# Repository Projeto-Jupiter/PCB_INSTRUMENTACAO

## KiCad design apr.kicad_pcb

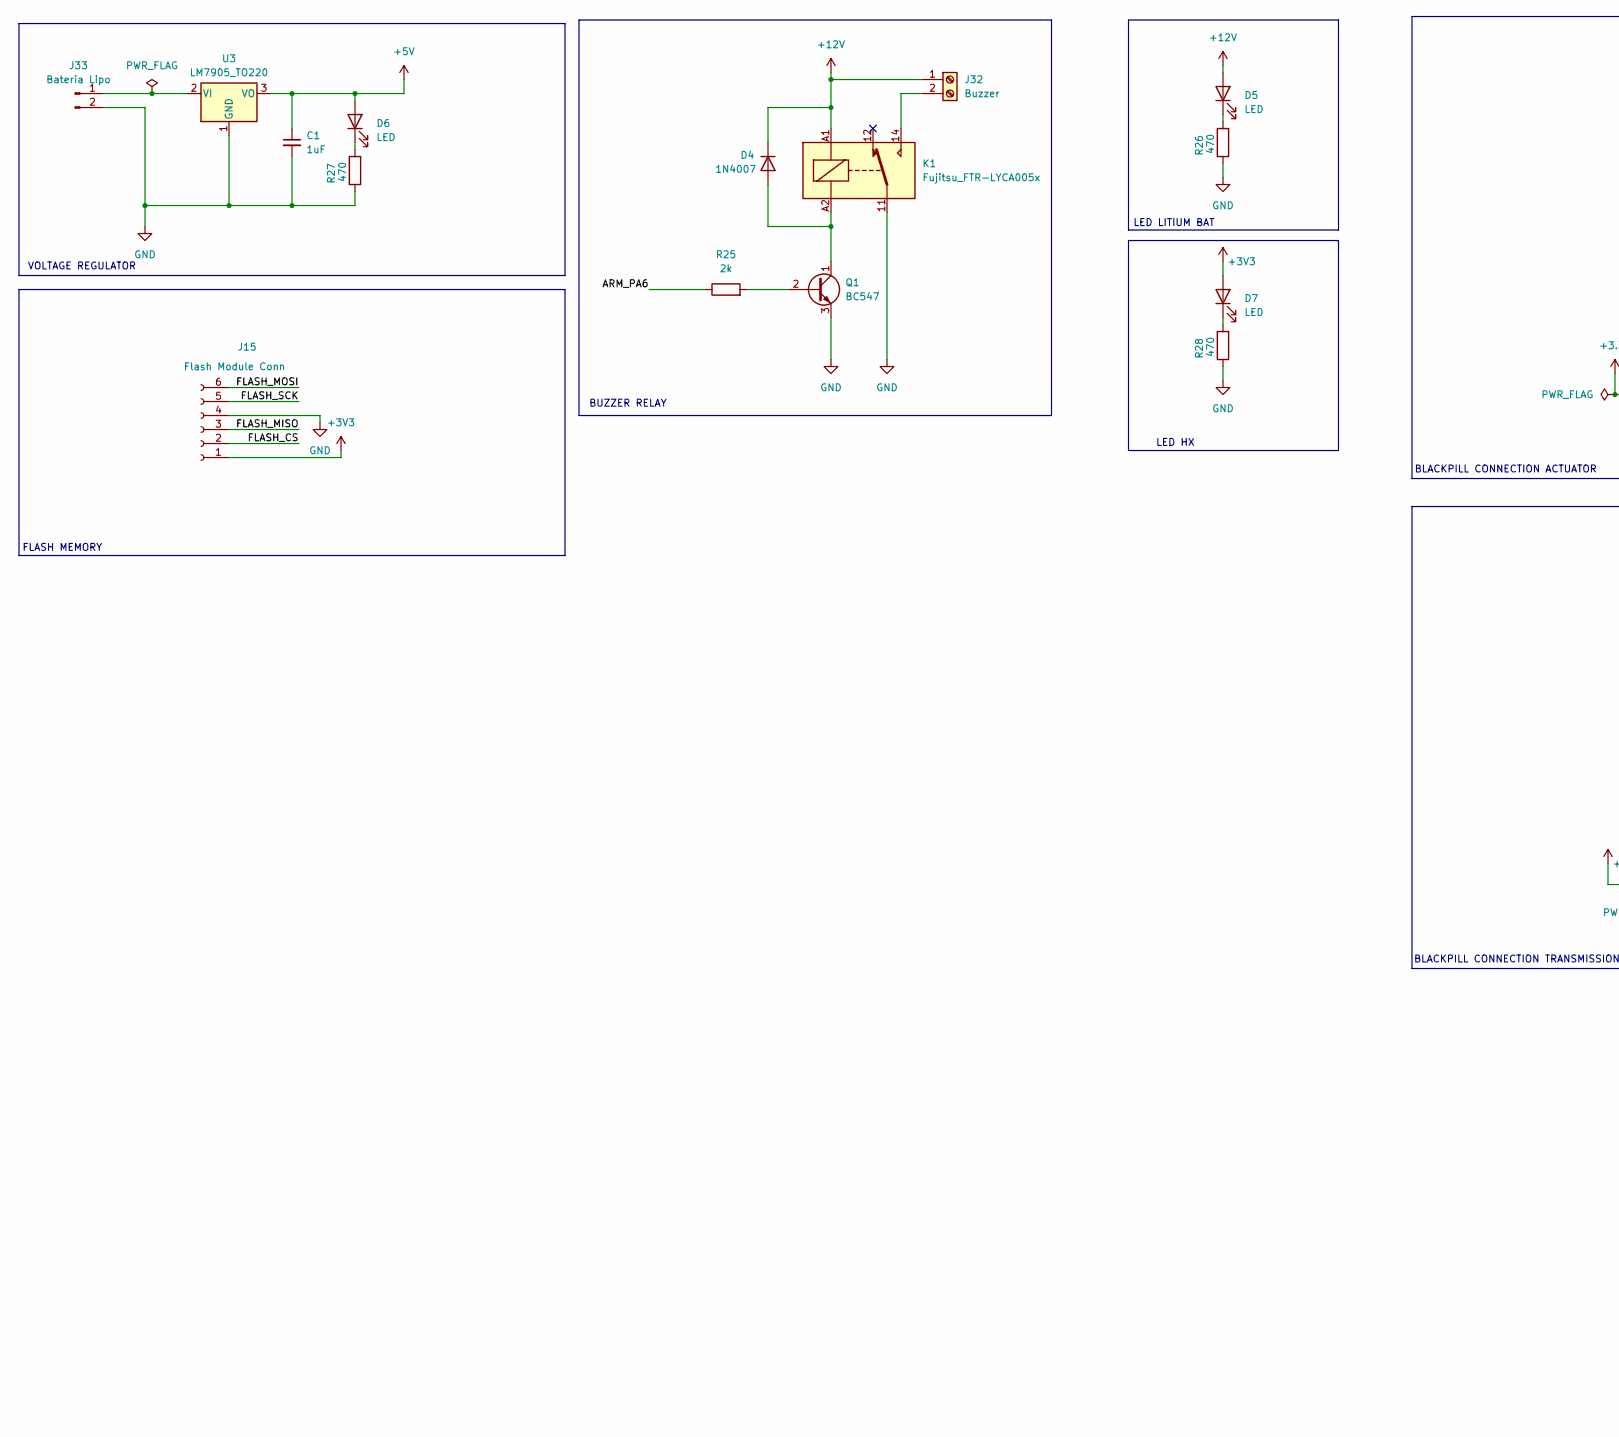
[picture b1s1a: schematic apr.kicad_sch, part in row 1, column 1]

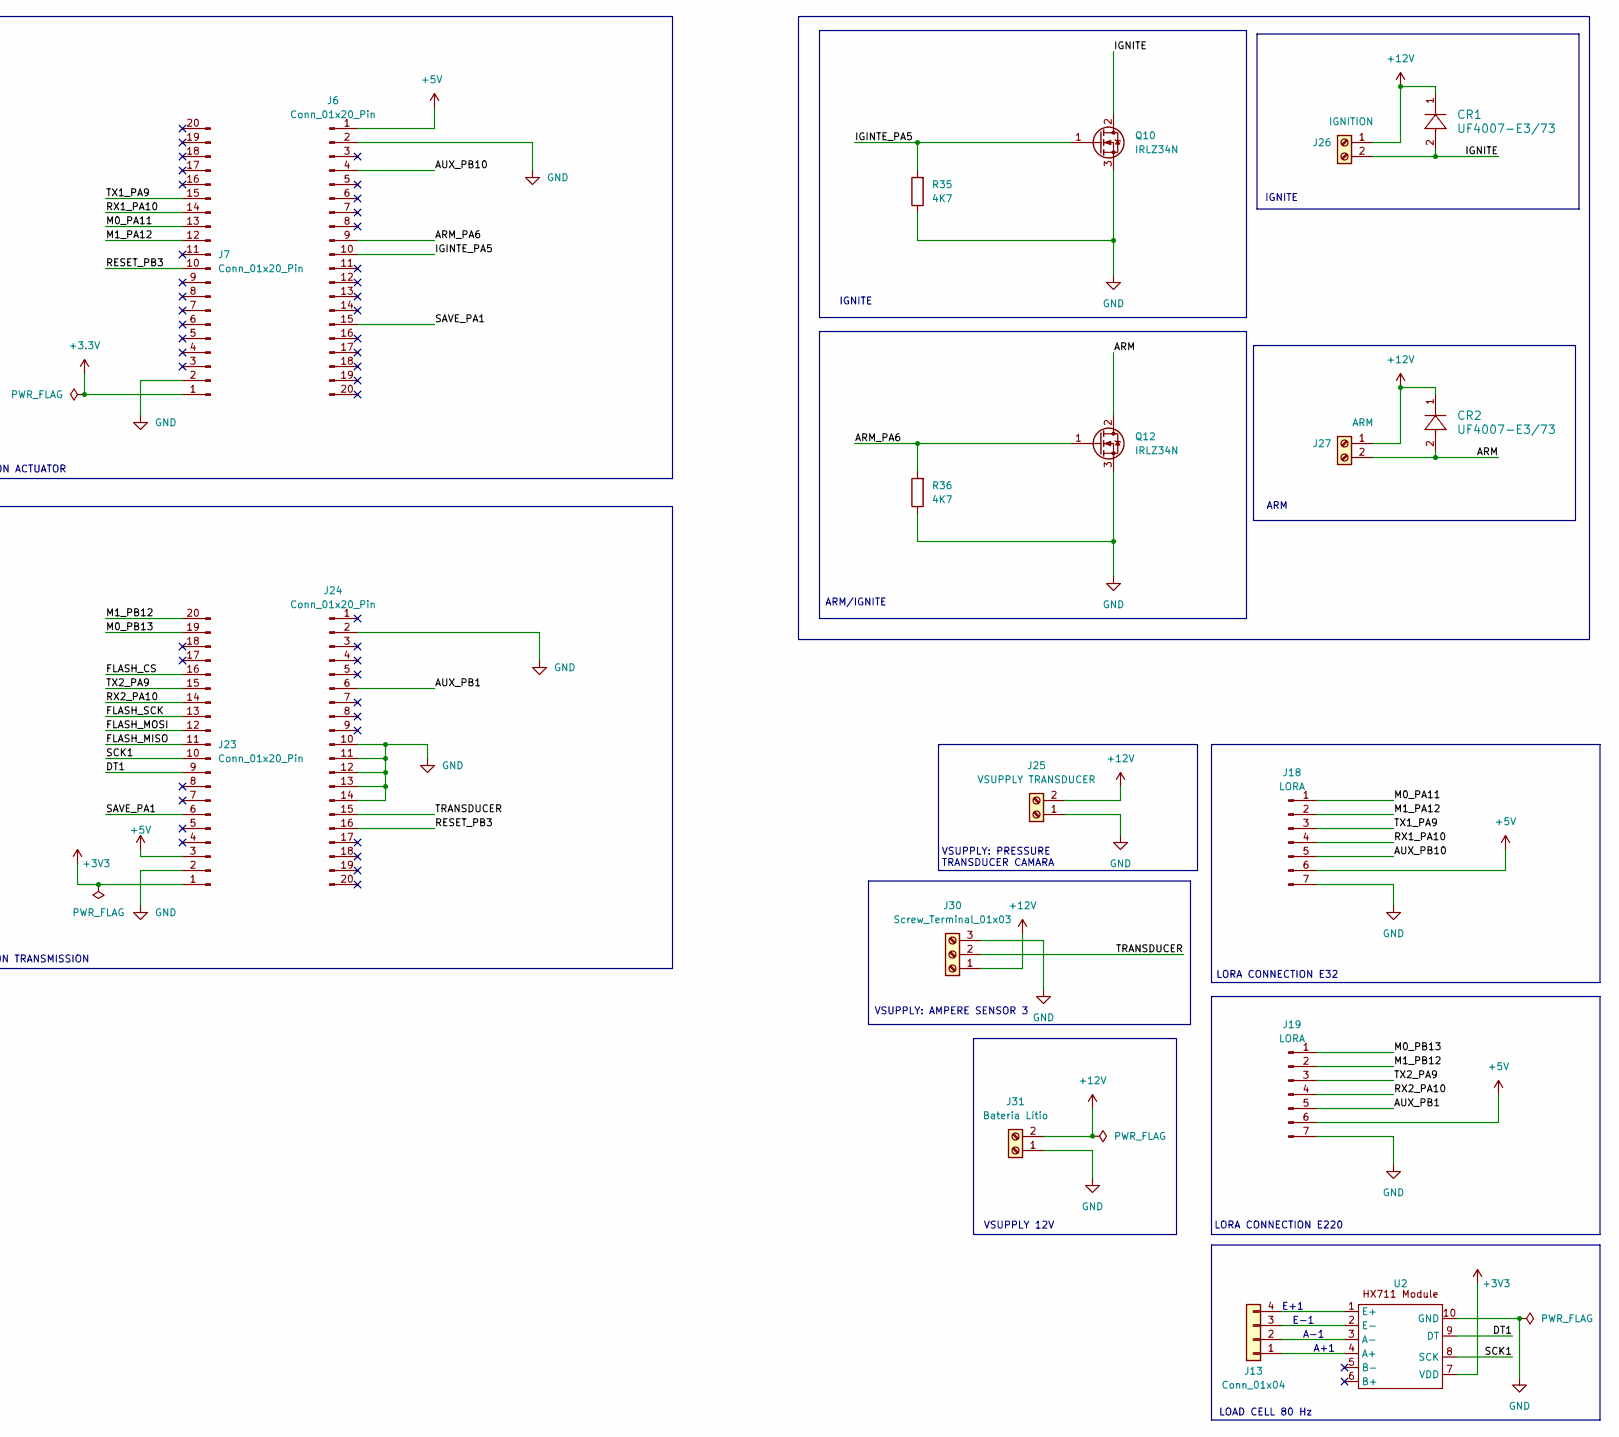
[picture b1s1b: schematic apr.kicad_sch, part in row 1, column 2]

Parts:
C1: 1uF; CP_Radial_D4.0mm_P1.50mm
CR1, CR2: UF4007-E3/73; D_A-405_P12.70mm_Horizontal
D4: 1N4007; D_DO-41_SOD81_P10.16mm_Horizontal
D5, D6, D7: LED; LED_D5.0mm
J6, J7, J23, J24: Conn_01x20_Pin; PinSocket_1x20_P2.54mm_Vertical
J13: Conn_01x04; TerminalBlock_bornier-4_P5.08mm
J15: Flash Module Conn; PinSocket_1x06_P2.54mm_Vertical
J18, J19: LORA; PinSocket_1x07_P2.54mm_Vertical
J25: VSUPPLY TRANSDUCER; Screw Terminal 3D
J26: IGNITION; Screw Terminal 3D
J27: ARM; Screw Terminal 3D
J30: Screw_Terminal_01x03; KT100-3PIN
J31: Bateria Lítio; Screw Terminal 3D
J32: Buzzer; Screw Terminal 3D
J33: Bateria Lipo; Screw Terminal 3D
K1: Fujitsu_FTR-LYCA005x; Relay_SPDT_Finder_36.11
Q1: BC547; TO-92_Inline
Q10, Q12: IRLZ34N; TO-220-3_Vertical
R25: 2k; R_0805_2012Metric
R26, R27, R28: 470; R_0805_2012Metric
R35, R36: 4K7; R_0805_2012Metric
U2: hx711
U3: LM7905_TO220; TO-220-3_Vertical

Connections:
+3.3V: J7.1
+3V3: D7.2 (A), J15.1, J23.1, U2.7 (VDD)
+5V: C1.1, D6.2 (A), J6.1, J18.6, J19.6, J23.3, U3.3 (VO)
+12V: CR1.1, CR2.1, D4.1 (K), D5.2 (A), J25.2, J26.1, J27.1, J30.1, J31.2, J32.1, K1.A1
/ARM: CR2.2, J27.2, Q12.2 (D)
/ARM_PA6: J6.9, Q12.1 (G), R25.1, R36.2
/AUX_PB1: J19.5, J24.6
/AUX_PB10: J6.4, J18.5
/DT1: J23.9, U2.9 (DT)
/FLASH_CS: J15.2, J23.16
/FLASH_MISO: J15.3, J23.11
/FLASH_MOSI: J15.6, J23.12
/FLASH_SCK: J15.5, J23.13
/IGINTE_PA5: J6.10, Q10.1 (G), R35.2
/IGNITE: CR1.2, J26.2, Q10.2 (D)
/M0_PA11: J7.13, J18.1
/M0_PB13: J19.1, J23.19
/M1_PA12: J7.12, J18.2
/M1_PB12: J19.2, J23.20
/RESET_PB3: J7.10, J24.16
/RX1_PA10: J7.14, J18.4
/RX2_PA10: J19.4, J23.14
/SAVE_PA1: J6.15, J23.6
/SCK1: J23.10, U2.8 (SCK)
/TRANSDUCER: J24.15, J30.2
/TX1_PA9: J7.15, J18.3
/TX2_PA9: J19.3, J23.15
GND: C1.2, J6.2, J7.2, J15.4, J18.7, J19.7, J23.2, J24.2, J24.10, J24.11, J24.12, J24.13, J24.14, J25.1, J30.3, J31.1, J33.2, K1.11, Q1.3 (E), Q10.3 (S), Q12.3 (S), R26.1, R27.1, R28.1, R35.1, R36.1, U2.10 (GND), U3.1 (GND)
unnamed: D4.2 (A), K1.A2, Q1.1 (C)
unnamed: D5.1 (K), R26.2
unnamed: D6.1 (K), R27.2
unnamed: D7.1 (K), R28.2
unnamed: J13.1, U2.4 (A+)
unnamed: J13.2, U2.3 (A-)
unnamed: J13.3, U2.2 (E-)
unnamed: J13.4, U2.1 (E+)
unnamed: J32.2, K1.14
unnamed: J33.1, U3.2 (VI)
unnamed: Q1.2 (B), R25.2

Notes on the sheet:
IGNITE
LOAD CELL 80 Hz
ARM/IGNITE
VOLTAGE REGULATOR
VSUPPLY: AMPERE SENSOR 3
LED HX
LORA CONNECTION E220
E+1
A-1
LORA CONNECTION E32
LED LITIUM BAT
VSUPPLY 12V
BUZZER RELAY
VSUPPLY: PRESSURE TRANSDUCER CAMARA
E-1
ARM
FLASH MEMORY
BLACKPILL CONNECTION TRANSMISSION
BLACKPILL CONNECTION ACTUATOR
A+1

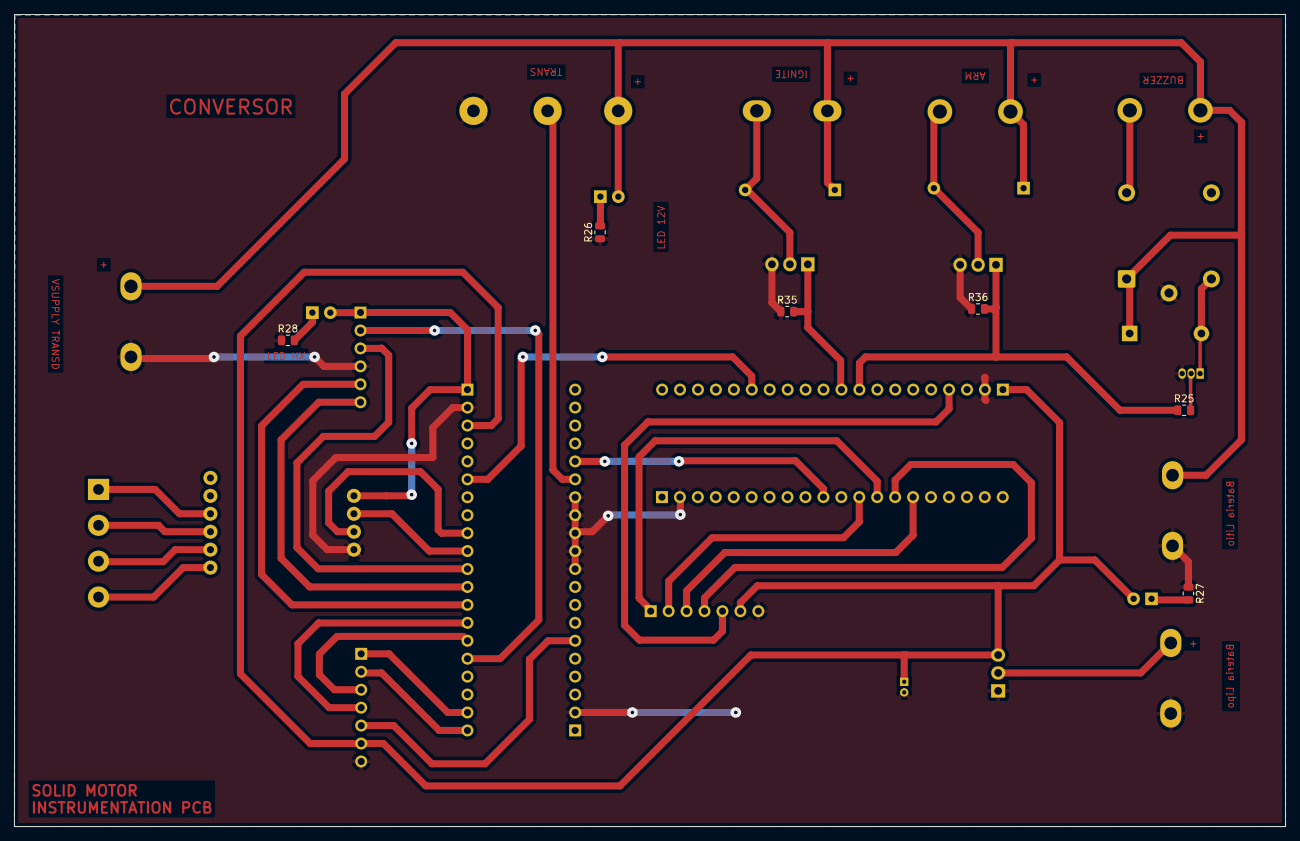
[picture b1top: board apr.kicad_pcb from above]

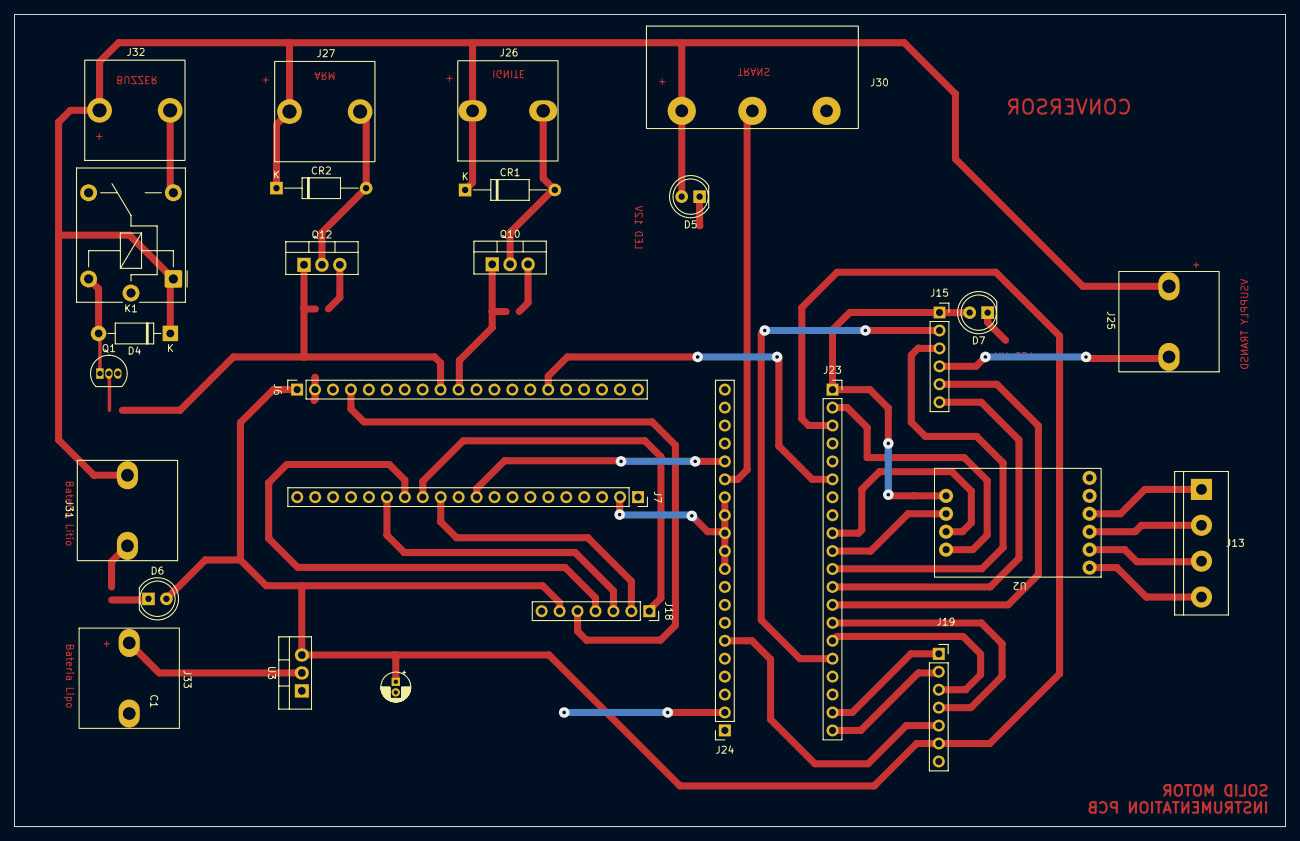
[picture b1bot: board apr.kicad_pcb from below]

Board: 2 copper layers, 180.0 x 115.0 mm, 34 parts (28 on the bottom side), 38 nets.

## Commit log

2025-02-24 Primeiro commit
2025-02-24 Revisão e ajustes
2025-02-25 Ajustes finais
2025-04-01 Atualizações do dia 29_03
2025-04-01 Troca do diodo para UF4007
2025-04-01 Adiciona Flash no esquemático
2025-04-03 Separação das alimentações
2025-04-04 Esquemático finalizado, Inicio do layout
2025-04-06 Versão 1.0 placa híbrido - 1 camada
2025-04-06 Primeiro commit nova versão
2025-04-06 Esquemático e Layout PCB Sólido
2025-04-08 Layout Final
